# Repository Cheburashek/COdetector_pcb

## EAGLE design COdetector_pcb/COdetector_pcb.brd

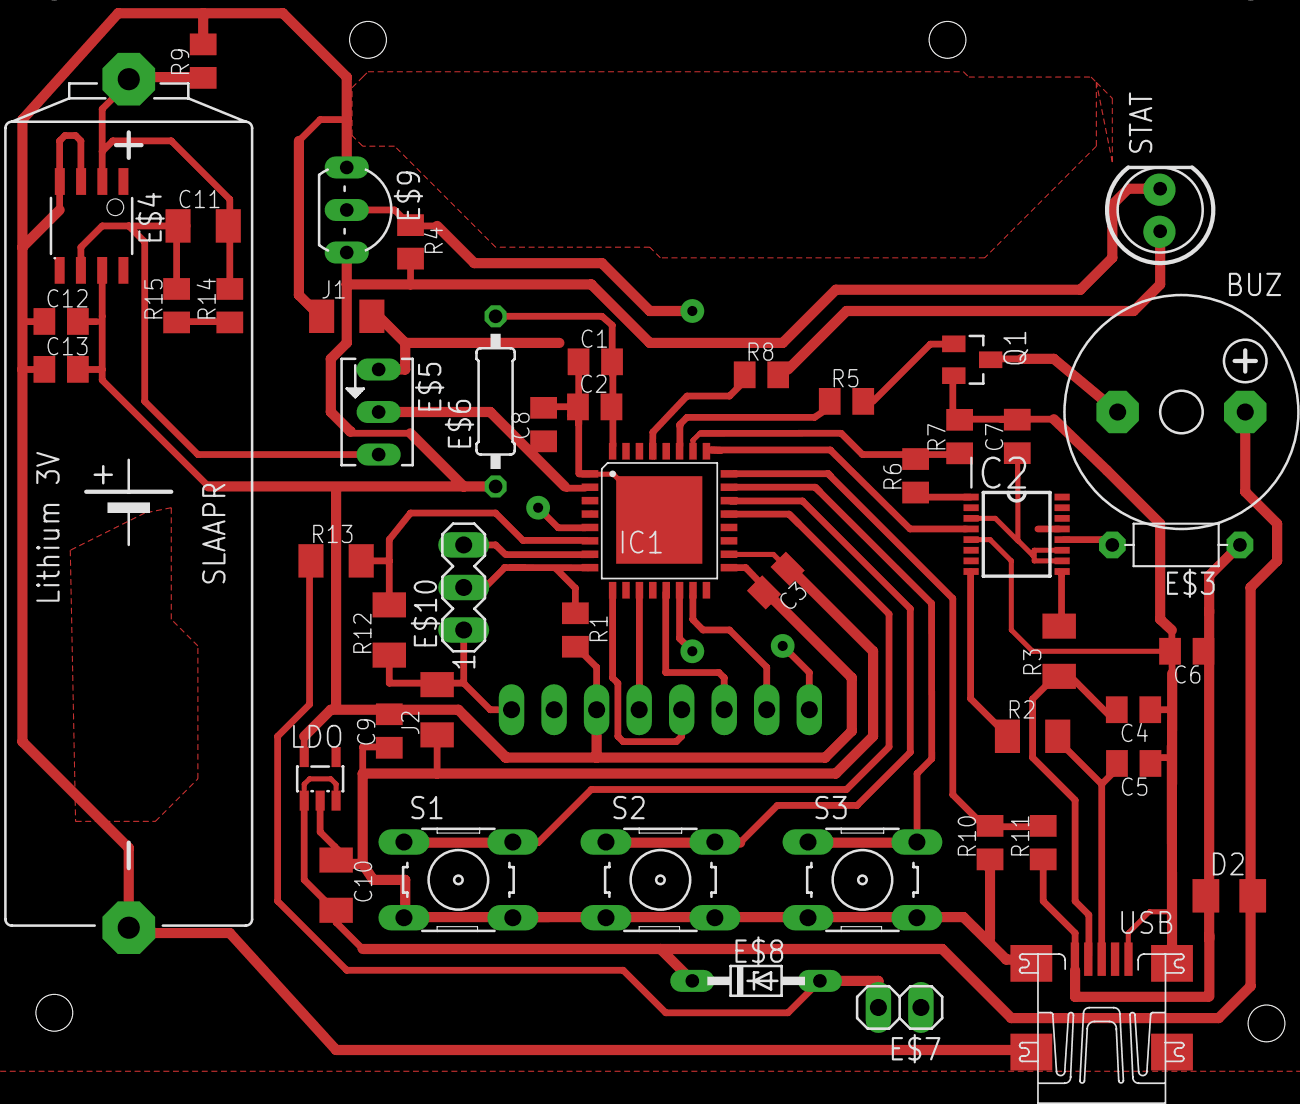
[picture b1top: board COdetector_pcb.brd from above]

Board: 2 copper layers, 51 parts (1 on the bottom side), 4 nets.

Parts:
BUZ: F/CM12P
C1, C2, C3, C4, C5, C6, C7, C8, C9, C12, C13: C0805K
C10, C11: C1206K
D2: M1206
E$1: SL-160AA/PR
E$2: MA08-1
E$3: R-7,5
E$4: 8S1
E$5: B64Y
E$6: 0207/10
E$7: 1X02
E$8: DO34Z7
E$9: TO92-LINE
E$10: MA03-1
IC1: VQFP32
IC2: SSOP16
J1, J2: C1206K
LDO: SOT23-5
Q1: SOT23
R1, R4, R5, R6, R7, R8, R9, R10, R11, R14, R15: C0805K
R2, R3, R12, R13: C1206K
S1, S2, S3: B3F-10XX
STAT: LED5MM
USB: UX60A-MB-5ST

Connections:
GND: C1.1, C3.1, C4.1, C5.1, C6.2, C7.2, C9.1, E$1.-, E$2.8, E$5.E, E$7.1, E$9.3, E$10.1, J2.1, J2.2, R7.1, R9.2, R12.1, USB.5, USB.M1, USB.M2, USB.M3, USB.M4
S$1: C2.1, C2.2
S$54: E$7.2, E$8.A
S$62: E$9.1, STAT.K

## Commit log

2015-10-27 First steps
2015-10-28 Almost done - digital part
2015-11-01 Added Vbat divider
2015-11-01 Start with layout
2015-11-02 Good job, Mr Tyran
2015-11-12 asdsadacsbhvddksxaxsd
2015-11-14 Prawie done
2015-11-14 Before ground wylawawing
2015-11-14 Super duper
2015-11-16 Ready for first probe of make
2015-11-17 Doone, checked, ready
2015-11-26 V3 RC
2015-12-14 Before sec version with all put togehter
2015-12-15 New Version, final
